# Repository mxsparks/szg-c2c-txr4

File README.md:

#  SYZYGY TXR4 Carrier-to-Carrier Adapter

A board-to-board connector supporting the high-speed SERDES I/O of two [SYZYGY](https://syzygyfpga.io)-compatible FPGA carrier cards, with an onboard PCIe reference clock.

## Overview

This card is intended as a development tool for high-speed board-to-board communication, e.g. between an Avnet [ZuBoard 1CG](https://www.avnet.com/wps/portal/us/products/avnet-boards/avnet-board-families/zuboard-1cg/zuboard-1cg) and a [ButterStick](https://github.com/butterstick-fpga/butterstick-hardware/blob/main/README.md). It routes the high-speed lanes (4 Tx, 4 Rx) as 100Ω AC-coupled differential pairs and provides an AC-coupled 100 MHz reference clock to both carrier cards. Additionally, it provides DC-coupled routing for the two general-purpose clocks (1 Tx, 1 Rx), 10 single-ended I/Os (routed as 5 differential pairs), and I2C. Jumper J3 allows one carrier card to optionally supply 5V power to the other. Jumper J4 enables spread-spectrum clocking (0.5% downshift).

## Note

This board is not SmartVIO-compatible and does not include a SYZYGY DNA MCU. Double-check that you're using compatible I/O standards on both connected FPGAs.

The high-speed lanes are polarity-inverted and partially lane-reversed, i.e. TX(0,1,2,3)p on J1 are connected to RX(2,3,0,1)n on J2. Depending on your FPGAs, this may limit your PCIe link to x2 instead of x4. It definitely prevents this card from being used to connect two SYZYGY TXR2 ports together (connecting a TXR4 port to a TXR2 port will still work).

## Fabrication

- Dimensions: 50 x 35 x 1.6 mm
- Standard 6-layer stackup from [JLCPCB](https://jlcpcb.com)
- Via in Pad required
- 6mil/6mil (0.15mm) trace/space
- 12mil (0.3mm) minimum drill size, 3mil (0.075mm) annular ring
- Layer In1.Cu: impedance-controlled to 100 Ω differential ± 10%.

## License

© 2023 mxsparks. Licensed under [CERN-OHL-P v2](https://ohwr.org/cern_ohl_p_v2.txt). Connector footprints from [SYZYGYfpga/pcb-templates](https://github.com/SYZYGYfpga/pcb-templates).

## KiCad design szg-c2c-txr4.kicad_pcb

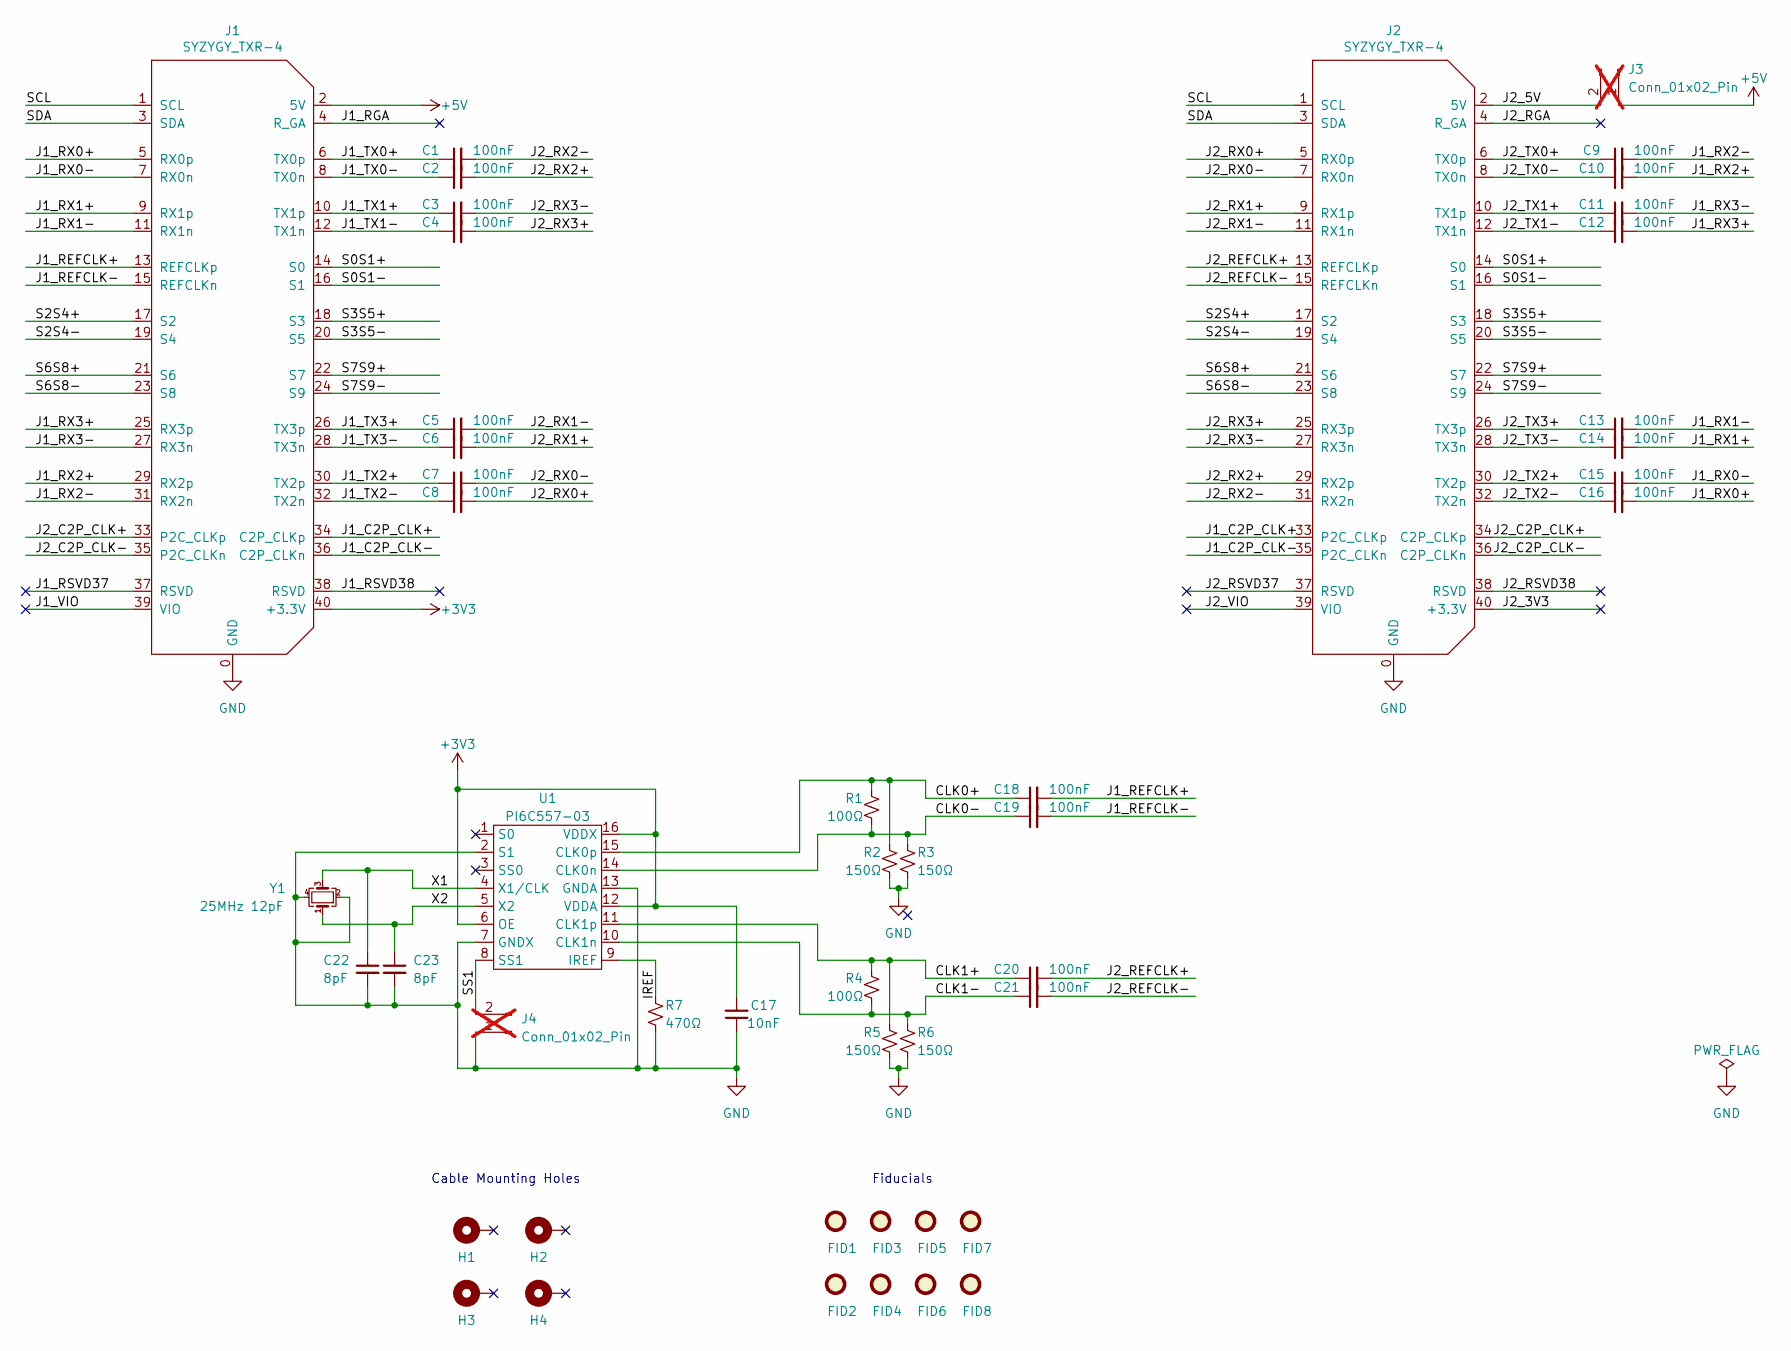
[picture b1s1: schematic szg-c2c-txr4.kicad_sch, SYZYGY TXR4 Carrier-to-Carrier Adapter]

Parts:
C1, C2, C3, C4, C5, C6, C7, C8, C9, C10, C11, C12, C13, C14, C15, C16, C18, C19, C20, C21: 100nF; C_0402_1005Metric
C17: 10nF; C_0402_1005Metric
C22, C23: 8pF; C_0402_1005Metric
FID1, FID2, FID3, FID4, FID5, FID6, FID7, FID8: Fiducial; Fiducial_1mm_Mask2mm
H1, H2, H3, H4: MountingHole_Pad; MountingHole_3.2mm_M3_6.5mm_Pad_TopBottom
J1, J2: SYZYGY_TXR-4; QTH-020-01-F-D-DP-A; Manufacturer_PN QTH-020-01-F-D-DP-A
J3, J4: Conn_01x02_Pin; PinHeader_1x02_P2.54mm_Vertical; not fitted
R1, R4: 100Ω; R_0402_1005Metric
R2, R3, R5, R6: 150Ω; R_0402_1005Metric
R7: 470Ω; R_0402_1005Metric
U1: PI6C557-03; TSSOP-16_4.4x5mm_P0.65mm
Y1: 25MHz 12pF; Crystal_SMD_3225-4Pin_3.2x2.5mm

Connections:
+3V3: C17.2, J1.40 (+3.3V), U1.6 (OE), U1.12 (VDDA), U1.16 (VDDX)
+5V: J1.2 (5V), J3.1
/CLK0+: C18.1, R1.1, R2.1, U1.15 (CLK0p)
/CLK0-: C19.1, R1.2, R3.1, U1.14 (CLK0n)
/CLK1+: C20.1, R4.1, R5.1, U1.11 (CLK1p)
/CLK1-: C21.1, R4.2, R6.1, U1.10 (CLK1n)
/IREF: R7.1, U1.9 (IREF)
/J1_C2P_CLK+: J1.34 (C2P_CLKp), J2.33 (P2C_CLKp)
/J1_C2P_CLK-: J1.36 (C2P_CLKn), J2.35 (P2C_CLKn)
/J1_REFCLK+: C18.2, J1.13 (REFCLKp)
/J1_REFCLK-: C19.2, J1.15 (REFCLKn)
/J1_RGA: J1.4 (R_GA)
/J1_RSVD37: J1.37 (RSVD)
/J1_RSVD38: J1.38 (RSVD)
/J1_RX0+: C16.2, J1.5 (RX0p)
/J1_RX0-: C15.2, J1.7 (RX0n)
/J1_RX1+: C14.2, J1.9 (RX1p)
/J1_RX1-: C13.2, J1.11 (RX1n)
/J1_RX2+: C10.2, J1.29 (RX2p)
/J1_RX2-: C9.2, J1.31 (RX2n)
/J1_RX3+: C12.2, J1.25 (RX3p)
/J1_RX3-: C11.2, J1.27 (RX3n)
/J1_TX0+: C1.1, J1.6 (TX0p)
/J1_TX0-: C2.1, J1.8 (TX0n)
/J1_TX1+: C3.1, J1.10 (TX1p)
/J1_TX1-: C4.1, J1.12 (TX1n)
/J1_TX2+: C7.1, J1.30 (TX2p)
/J1_TX2-: C8.1, J1.32 (TX2n)
/J1_TX3+: C5.1, J1.26 (TX3p)
/J1_TX3-: C6.1, J1.28 (TX3n)
/J1_VIO: J1.39 (VIO)
/J2_3V3: J2.40 (+3.3V)
/J2_5V: J2.2 (5V), J3.2
/J2_C2P_CLK+: J1.33 (P2C_CLKp), J2.34 (C2P_CLKp)
/J2_C2P_CLK-: J1.35 (P2C_CLKn), J2.36 (C2P_CLKn)
/J2_REFCLK+: C20.2, J2.13 (REFCLKp)
/J2_REFCLK-: C21.2, J2.15 (REFCLKn)
/J2_RGA: J2.4 (R_GA)
/J2_RSVD37: J2.37 (RSVD)
/J2_RSVD38: J2.38 (RSVD)
/J2_RX0+: C8.2, J2.5 (RX0p)
/J2_RX0-: C7.2, J2.7 (RX0n)
/J2_RX1+: C6.2, J2.9 (RX1p)
/J2_RX1-: C5.2, J2.11 (RX1n)
/J2_RX2+: C2.2, J2.29 (RX2p)
/J2_RX2-: C1.2, J2.31 (RX2n)
/J2_RX3+: C4.2, J2.25 (RX3p)
/J2_RX3-: C3.2, J2.27 (RX3n)
/J2_TX0+: C9.1, J2.6 (TX0p)
/J2_TX0-: C10.1, J2.8 (TX0n)
/J2_TX1+: C11.1, J2.10 (TX1p)
/J2_TX1-: C12.1, J2.12 (TX1n)
/J2_TX2+: C15.1, J2.30 (TX2p)
/J2_TX2-: C16.1, J2.32 (TX2n)
/J2_TX3+: C13.1, J2.26 (TX3p)
/J2_TX3-: C14.1, J2.28 (TX3n)
/J2_VIO: J2.39 (VIO)
/S0S1+: J1.14 (S0), J2.14 (S0)
/S0S1-: J1.16 (S1), J2.16 (S1)
/S2S4+: J1.17 (S2), J2.17 (S2)
/S2S4-: J1.19 (S4), J2.19 (S4)
/S3S5+: J1.18 (S3), J2.18 (S3)
/S3S5-: J1.20 (S5), J2.20 (S5)
/S6S8+: J1.21 (S6), J2.21 (S6)
/S6S8-: J1.23 (S8), J2.23 (S8)
/S7S9+: J1.22 (S7), J2.22 (S7)
/S7S9-: J1.24 (S9), J2.24 (S9)
/SCL: J1.1 (SCL), J2.1 (SCL)
/SDA: J1.3 (SDA), J2.3 (SDA)
/SS1: J4.2, U1.8 (SS1)
/X1: C22.1, U1.4 (X1/CLK), Y1.3
/X2: C23.1, U1.5 (X2), Y1.1
GND: C17.1, C22.2, C23.2, J1.0 (GND), J2.0 (GND), J4.1, R2.2, R3.2, R5.2, R6.2, R7.2, U1.2 (S1), U1.7 (GNDX), U1.13 (GNDA), Y1.2, Y1.4

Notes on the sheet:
Cable Mounting Holes
Fiducials

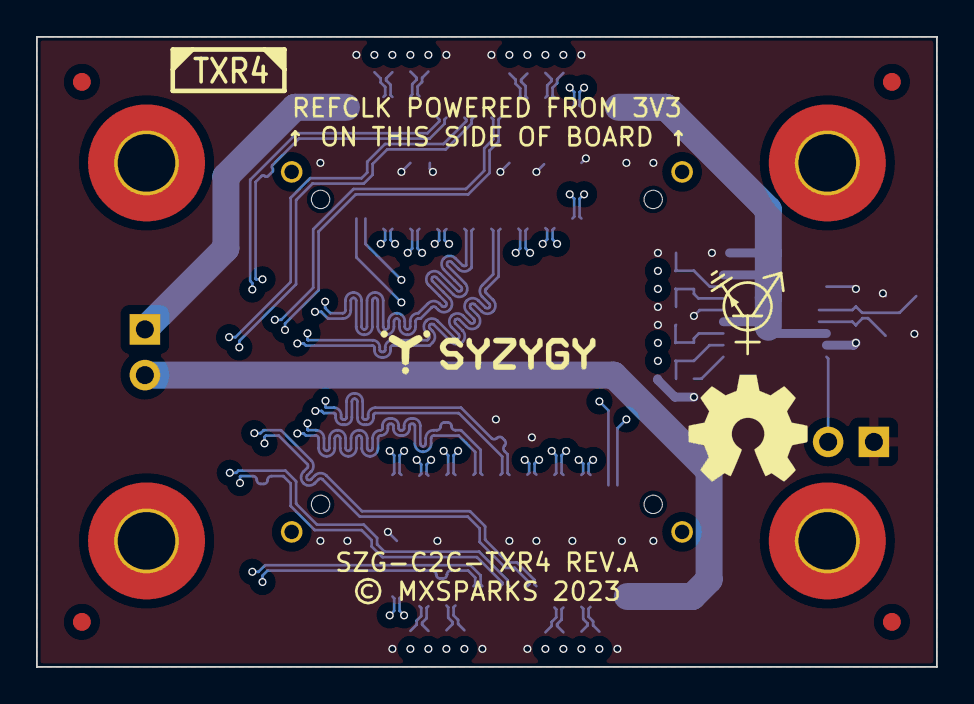
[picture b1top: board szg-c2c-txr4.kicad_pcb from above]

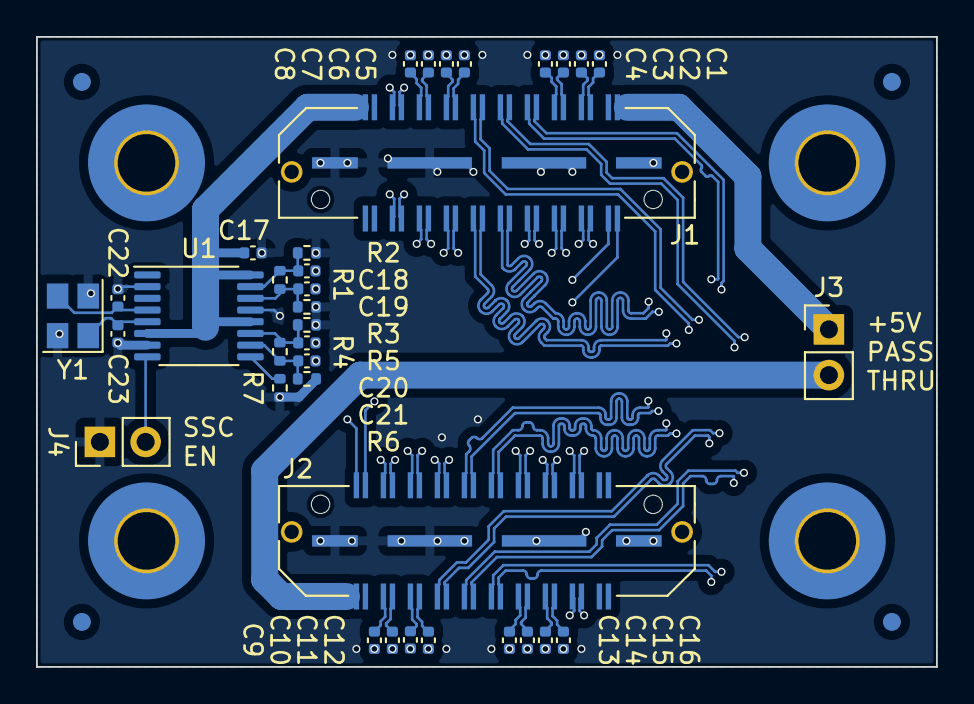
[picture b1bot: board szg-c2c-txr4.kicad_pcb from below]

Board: 6 copper layers, 50.0 x 35.0 mm, 50 parts (40 on the bottom side), 64 nets.

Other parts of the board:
G**: Transistor-Logo
G**#2: SYZYGY_STD_Logo; SYZYGY_TXR4_Logo

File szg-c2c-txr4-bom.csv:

Quantity,Reference Designators,JLCPCB Part #,Description,Manufacturer,Manufacturer Part #
20,"C1,C2,C3,C4,C5,C6,C7,C8,C9,C10,C11,C12,C13,C14,C15,C16,C18,C19,C20,C21",C1525,16V 100nF X7R ±10% 0402 Multilayer Ceramic Capacitors MLCC - SMD/SMT ROHS,Samsung,CL05B104KO5NNNC
1,C17,C15195,50V 10nF X7R ±10% 0402 Multilayer Ceramic Capacitors MLCC - SMD/SMT ROHS,Samsung,CL05B103KB5NNNC
2,"C22,C23",C1864375,50V 8pF C0G ±1% 0402 Multilayer Ceramic Capacitors MLCC - SMD/SMT ROHS,Murata,GCM1555C1H8R0FA16D
2,"J1,J2",C3654517,"40 Position Connector Differential Pair Array, Male Surface Mount Gold",Samtec,QTH-020-01-F-D-DP-A-K-TR
2,"J3,J4",C390678,"3A Straight Square Pins 2.5mm 6.1mm 3mm 2 2.54mm Single Row Black Brass 1x2P Plugin,P=2.54mm Pin Headers ROHS",Pinrex,210-91-02GB01
2,"R1,R4",C25076,62.5mW Thick Film Resistors ±1% 100Ω 0402 Chip Resistor - Surface Mount ROHS,Uniroyal,0402WGF1000TCE
4,"R2,R3,R5,R6",C25082,62.5mW Thick Film Resistors ±1% 150Ω 0402 Chip Resistor - Surface Mount ROHS,Uniroyal,0402WGF1500TCE
1,R7,C25117,62.5mW Thick Film Resistors ±1% 470Ω 0402 Chip Resistor - Surface Mount ROHS,Uniroyal,0402WGF4700TCE
1,U1,C500785,200MHz 2 TSSOP-16 Clock Generators / Frequency Synthesizers / PLL ROHS,Diodes Inc.,PI6C557-03LEX
1,Y1,C9006,25MHz 12pF ±10ppm ±30ppm SMD3225-4P Crystals ROHS,Yangxing Tech,X322525MOB4SI

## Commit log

2023-05-03 README.md: fix typo
2023-05-26 change REFCLK circuit due to parts availability

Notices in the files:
szg-c2c-txr4.kicad_pcb:
© MXSPARKS 2023
